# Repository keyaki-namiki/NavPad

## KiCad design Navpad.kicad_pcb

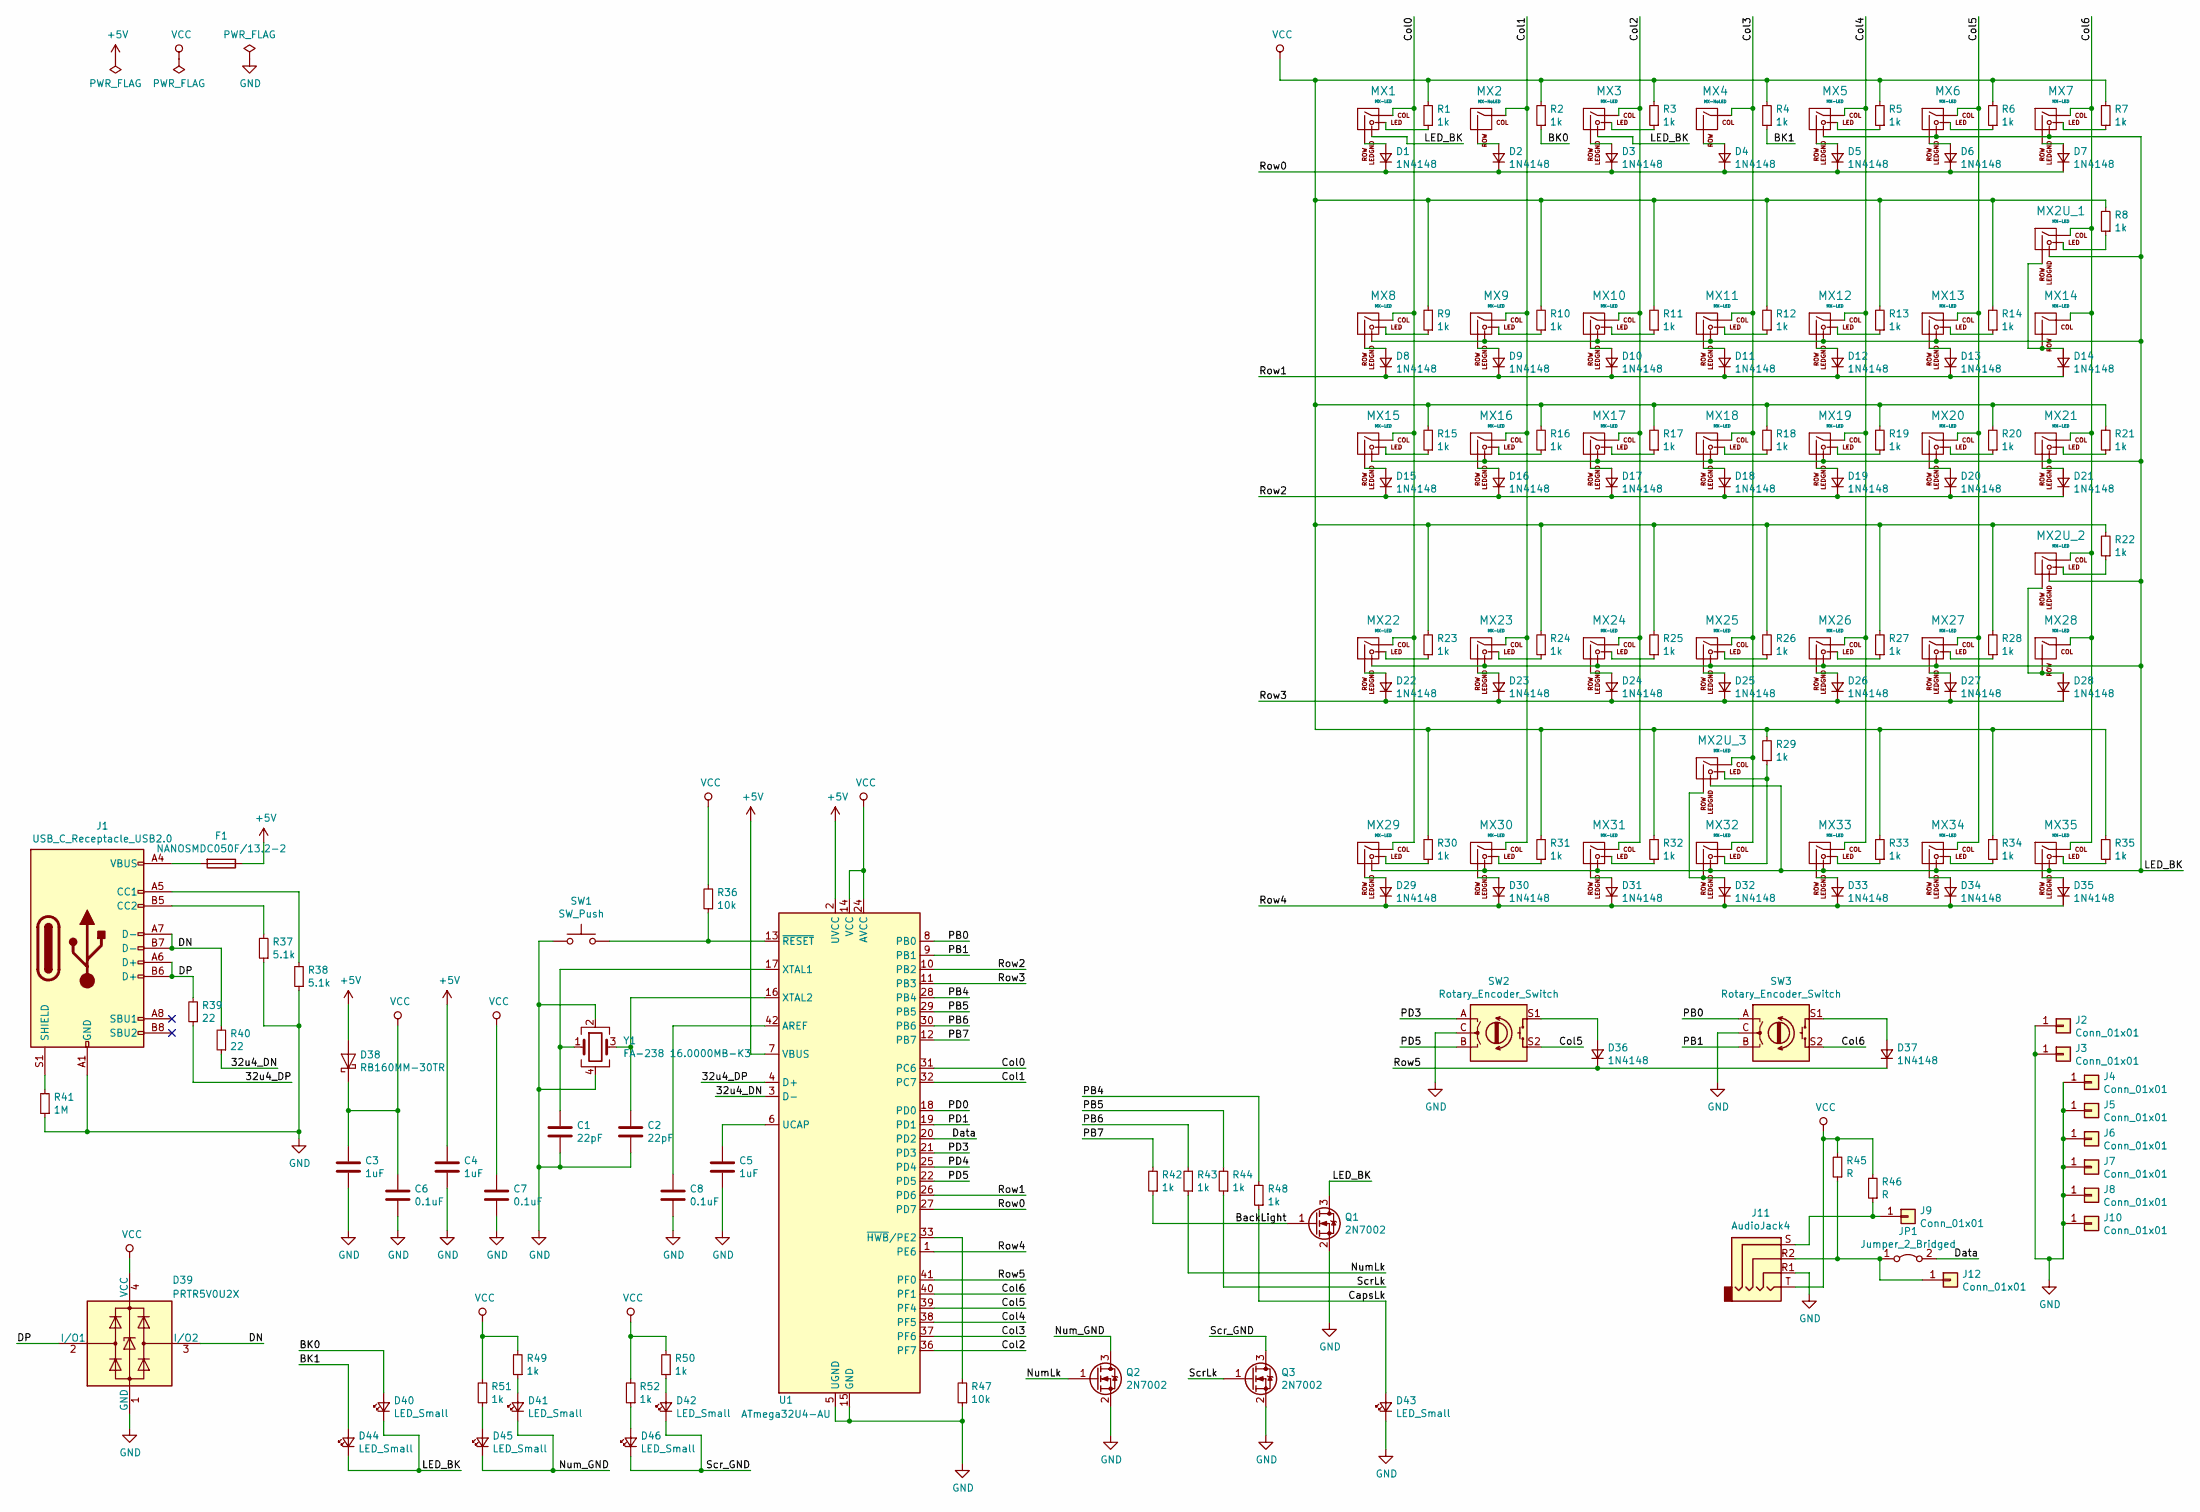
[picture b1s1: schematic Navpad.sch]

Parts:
C1, C2: 22pF; C_0603_1608Metric_Pad1.05x0.95mm_HandSolder
C3, C4, C5: 1uF; C_0603_1608Metric_Pad1.05x0.95mm_HandSolder
C6, C7, C8: 0.1uF; C_0603_1608Metric_Pad1.05x0.95mm_HandSolder
D1, D2, D3, D4, D5, D6, D7, D8, D9, D10, D11, D12, D13, D14, D15, D16, D17, D18, D19, D20, D21, D22, D23, D24, D25, D26, D27, D28, D29, D30, D31, D32, D33, D34, D35, D36, D37: 1N4148; D_SOD-123F
D38: RB160MM-30TR; D_SOD-123F
D39: PRTR5V0U2X; SOT-143
D40, D41, D42, D43, D44, D45, D46: LED_Small; LED_0603_1608Metric_Pad1.05x0.95mm_HandSolder
F1: NANOSMDC050F/13.2-2; Fuse_1206_3216Metric_Pad1.42x1.75mm_HandSolder
J1: USB_C_Receptacle_USB2.0; USB_C_Receptacle_GCT_USB4085
J2, J3: Conn_01x01; TestPoint_Plated_Hole_D5.0mm
J4, J5, J6, J7, J8, J10: Conn_01x01; MountingHole_2.2mm_M2_Pad
J9, J12: Conn_01x01; TestPoint_THTPad_1.0x1.0mm_Drill0.5mm
J11: AudioJack4; 4pin_jack
JP1: Jumper_2_Bridged; SolderJumper-2_P1.3mm_Bridged_Pad1.0x1.5mm
MX1, MX3, MX5, MX6, MX7, MX8, MX9, MX10, MX11, MX12, MX13, MX15, MX16, MX17, MX18, MX19, MX20, MX21, MX22, MX23, MX24, MX25, MX26, MX27, MX29, MX30, MX31, MX32, MX33, MX34, MX35: MX-LED; MXOnly-1U
MX2, MX4: MX-NoLED; MXOnly-1U-NoLED
MX2U_1, MX2U_2, MX2U_3: MX-LED; MXOnly-2U-ReversedStabilizers
MX14, MX28: MX-LED; MXOnly-1U-NoLED
Q1, Q2, Q3: 2N7002; SOT-23
R1, R2, R3, R4, R5, R6, R7, R8, R9, R10, R11, R12, R13, R14, R15, R16, R17, R18, R19, R20, R21, R22, R23, R24, R25, R26, R27, R28, R29, R30, R31, R32, R33, R34, R35, R42, R43, R44, R48, R49, R50, R51, R52: 1k; R_0603_1608Metric_Pad1.05x0.95mm_HandSolder
R36, R47: 10k; R_0603_1608Metric_Pad1.05x0.95mm_HandSolder
R37, R38: 5.1k; R_0603_1608Metric_Pad1.05x0.95mm_HandSolder
R39, R40: 22; R_0603_1608Metric_Pad1.05x0.95mm_HandSolder
R41: 1M; R_0603_1608Metric_Pad1.05x0.95mm_HandSolder
R45, R46: R; R_0603_1608Metric_Pad1.05x0.95mm_HandSolder
SW1: SW_Push; SW_SPST_TL3342
SW2, SW3: Rotary_Encoder_Switch; RotaryEncoder_Alps_EC11E-Switch_Vertical_H20mm
U1: ATmega32U4-AU; TQFP-44_10x10mm_P0.8mm
Y1: FA-238 16.0000MB-K3; Crystal_SMD_SeikoEpson_FA238-4Pin_3.2x2.5mm_HandSoldering

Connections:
+5V: C4.1, D38.2 (A), F1.1, U1.2 (UVCC), U1.7 (VBUS)
/32u4_DN: R40.1, U1.3 (D-)
/32u4_DP: R39.1, U1.4 (D+)
/BK0: D40.2 (A), R2.1
/BK1: D44.2 (A), R4.1
/BackLight: Q1.1 (G), R42.1
/CapsLk: D43.2 (A), R48.1
/Col0: MX1.1 (COL), MX8.1 (COL), MX15.1 (COL), MX22.1 (COL), MX29.1 (COL), U1.31 (PC6)
/Col1: MX2.1 (COL), MX9.1 (COL), MX16.1 (COL), MX23.1 (COL), MX30.1 (COL), U1.32 (PC7)
/Col2: MX3.1 (COL), MX10.1 (COL), MX17.1 (COL), MX24.1 (COL), MX31.1 (COL), U1.36 (PF7)
/Col3: MX2U_3.1 (COL), MX4.1 (COL), MX11.1 (COL), MX18.1 (COL), MX25.1 (COL), MX32.1 (COL), U1.37 (PF6)
/Col4: MX5.1 (COL), MX12.1 (COL), MX19.1 (COL), MX26.1 (COL), MX33.1 (COL), U1.38 (PF5)
/Col5: MX6.1 (COL), MX13.1 (COL), MX20.1 (COL), MX27.1 (COL), MX34.1 (COL), SW2.S2, U1.39 (PF4)
/Col6: MX2U_1.1 (COL), MX2U_2.1 (COL), MX7.1 (COL), MX14.1 (COL), MX21.1 (COL), MX28.1 (COL), MX35.1 (COL), SW3.S2, U1.40 (PF1)
/DN: D39.3 (I/O2), J1.A7 (D-), J1.B7 (D-), R40.2
/DP: D39.2 (I/O1), J1.A6 (D+), J1.B6 (D+), R39.2
/Data: JP1.2 (B), U1.20 (PD2)
/LED_BK: D40.1 (K), D44.1 (K), MX1.4 (LEDGND), MX2U_1.4 (LEDGND), MX2U_2.4 (LEDGND), MX2U_3.4 (LEDGND), MX3.4 (LEDGND), MX5.4 (LEDGND), MX6.4 (LEDGND), MX7.4 (LEDGND), MX8.4 (LEDGND), MX9.4 (LEDGND), MX10.4 (LEDGND), MX11.4 (LEDGND), MX12.4 (LEDGND), MX13.4 (LEDGND), MX15.4 (LEDGND), MX16.4 (LEDGND), MX17.4 (LEDGND), MX18.4 (LEDGND), MX19.4 (LEDGND), MX20.4 (LEDGND), MX21.4 (LEDGND), MX22.4 (LEDGND), MX23.4 (LEDGND), MX24.4 (LEDGND), MX25.4 (LEDGND), MX26.4 (LEDGND), MX27.4 (LEDGND), MX29.4 (LEDGND), MX30.4 (LEDGND), MX31.4 (LEDGND), MX32.4 (LEDGND), MX33.4 (LEDGND), MX34.4 (LEDGND), MX35.4 (LEDGND), Q1.3 (D)
/NumLk: Q2.1 (G), R43.1
/Num_GND: D41.1 (K), D45.1 (K), Q2.3 (D)
/PB0: SW3.A, U1.8 (PB0)
/PB1: SW3.B, U1.9 (PB1)
/PB4: R48.2, U1.28 (PB4)
/PB5: R44.2, U1.29 (PB5)
/PB6: R43.2, U1.30 (PB6)
/PB7: R42.2, U1.12 (PB7)
/PD0: U1.18 (PD0)
/PD1: U1.19 (PD1)
/PD3: SW2.A, U1.21 (PD3)
/PD4: U1.25 (PD4)
/PD5: SW2.B, U1.22 (PD5)
/Row0: D1.1 (K), D2.1 (K), D3.1 (K), D4.1 (K), D5.1 (K), D6.1 (K), D7.1 (K), U1.27 (PD7)
/Row1: D8.1 (K), D9.1 (K), D10.1 (K), D11.1 (K), D12.1 (K), D13.1 (K), D14.1 (K), U1.26 (PD6)
/Row2: D15.1 (K), D16.1 (K), D17.1 (K), D18.1 (K), D19.1 (K), D20.1 (K), D21.1 (K), U1.10 (PB2)
/Row3: D22.1 (K), D23.1 (K), D24.1 (K), D25.1 (K), D26.1 (K), D27.1 (K), D28.1 (K), U1.11 (PB3)
/Row4: D29.1 (K), D30.1 (K), D31.1 (K), D32.1 (K), D33.1 (K), D34.1 (K), D35.1 (K), U1.1 (PE6)
/Row5: D36.1 (K), D37.1 (K), U1.41 (PF0)
/ScrLk: Q3.1 (G), R44.1
/Scr_GND: D42.1 (K), D46.1 (K), Q3.3 (D)
GND: C1.2, C2.2, C3.2, C4.2, C5.2, C6.2, C7.2, C8.2, D39.1 (GND), D43.1 (K), J1.A1 (GND), J1.A12 (GND), J1.B1 (GND), J1.B12 (GND), J2.1, J3.1, J4.1, J5.1, J6.1, J7.1, J8.1, J10.1, J11.R1, Q1.2 (S), Q2.2 (S), Q3.2 (S), R37.1, R38.1, R41.1, R47.1, SW1.1, SW2.C, SW3.C, U1.5 (UGND), U1.15 (GND), U1.23 (GND), U1.35 (GND), U1.43 (GND), Y1.2, Y1.4
unnamed: C1.1, U1.17 (XTAL1), Y1.1
unnamed: C2.1, U1.16 (XTAL2), Y1.3
unnamed: C5.1, U1.6 (UCAP)
unnamed: C8.1, U1.42 (AREF)
unnamed: D1.2 (A), MX1.2 (ROW)
unnamed: D2.2 (A), MX2.2 (ROW)
unnamed: D3.2 (A), MX3.2 (ROW)
unnamed: D4.2 (A), MX4.2 (ROW)
unnamed: D5.2 (A), MX5.2 (ROW)
unnamed: D6.2 (A), MX6.2 (ROW)
unnamed: D7.2 (A), MX7.2 (ROW)
unnamed: D8.2 (A), MX8.2 (ROW)
unnamed: D9.2 (A), MX9.2 (ROW)
unnamed: D10.2 (A), MX10.2 (ROW)
unnamed: D11.2 (A), MX11.2 (ROW)
unnamed: D12.2 (A), MX12.2 (ROW)
unnamed: D13.2 (A), MX13.2 (ROW)
unnamed: D14.2 (A), MX2U_1.2 (ROW), MX14.2 (ROW)
unnamed: D15.2 (A), MX15.2 (ROW)
unnamed: D16.2 (A), MX16.2 (ROW)
unnamed: D17.2 (A), MX17.2 (ROW)
unnamed: D18.2 (A), MX18.2 (ROW)
unnamed: D19.2 (A), MX19.2 (ROW)
unnamed: D20.2 (A), MX20.2 (ROW)
unnamed: D21.2 (A), MX21.2 (ROW)
unnamed: D22.2 (A), MX22.2 (ROW)
unnamed: D23.2 (A), MX23.2 (ROW)
unnamed: D24.2 (A), MX24.2 (ROW)
unnamed: D25.2 (A), MX25.2 (ROW)
unnamed: D26.2 (A), MX26.2 (ROW)
unnamed: D27.2 (A), MX27.2 (ROW)
unnamed: D28.2 (A), MX2U_2.2 (ROW), MX28.2 (ROW)
unnamed: D29.2 (A), MX29.2 (ROW)
unnamed: D30.2 (A), MX30.2 (ROW)
unnamed: D31.2 (A), MX31.2 (ROW)
unnamed: D32.2 (A), MX2U_3.2 (ROW), MX32.2 (ROW)
unnamed: D33.2 (A), MX33.2 (ROW)
unnamed: D34.2 (A), MX34.2 (ROW)
unnamed: D35.2 (A), MX35.2 (ROW)
unnamed: D36.2 (A), SW2.S1
unnamed: D37.2 (A), SW3.S1
unnamed: D41.2 (A), R49.1
unnamed: D42.2 (A), R50.1
unnamed: D45.2 (A), R51.1
unnamed: D46.2 (A), R52.1
unnamed: F1.2, J1.A4 (VBUS), J1.A9 (VBUS), J1.B4 (VBUS), J1.B9 (VBUS)
unnamed: J1.A5 (CC1), R38.2
unnamed: J1.B5 (CC2), R37.2
unnamed: J1.S1 (SHIELD), R41.2
unnamed: J11.R2, J12.1, JP1.1 (A), R45.1
unnamed: J9.1, J11.S, R46.1
unnamed: MX1.3 (LED), R1.1
unnamed: MX2U_1.3 (LED), R8.1
unnamed: MX2U_2.3 (LED), R22.1
unnamed: MX2U_3.3 (LED), MX32.3 (LED), R29.1
unnamed: MX3.3 (LED), R3.1
unnamed: MX5.3 (LED), R5.1
unnamed: MX6.3 (LED), R6.1
unnamed: MX7.3 (LED), R7.1
unnamed: MX8.3 (LED), R9.1
unnamed: MX9.3 (LED), R10.1
unnamed: MX10.3 (LED), R11.1
unnamed: MX11.3 (LED), R12.1
unnamed: MX12.3 (LED), R13.1
unnamed: MX13.3 (LED), R14.1
unnamed: MX15.3 (LED), R15.1
unnamed: MX16.3 (LED), R16.1
unnamed: MX17.3 (LED), R17.1
unnamed: MX18.3 (LED), R18.1
unnamed: MX19.3 (LED), R19.1
unnamed: MX20.3 (LED), R20.1
unnamed: MX21.3 (LED), R21.1
unnamed: MX22.3 (LED), R23.1
unnamed: MX23.3 (LED), R24.1
unnamed: MX24.3 (LED), R25.1
unnamed: MX25.3 (LED), R26.1
unnamed: MX26.3 (LED), R27.1
unnamed: MX27.3 (LED), R28.1
unnamed: MX29.3 (LED), R30.1
unnamed: MX30.3 (LED), R31.1
unnamed: MX31.3 (LED), R32.1
unnamed: MX33.3 (LED), R33.1
unnamed: MX34.3 (LED), R34.1
unnamed: MX35.3 (LED), R35.1
unnamed: R36.1, SW1.2, U1.13 (~RESET)
unnamed: R47.2, U1.33 (~HWB~/PE2)
VCC: C3.1, C6.1, C7.1, D38.1 (K), D39.4 (VCC), J11.T, R1.2, R2.2, R3.2, R4.2, R5.2, R6.2, R7.2, R8.2, R9.2, R10.2, R11.2, R12.2, R13.2, R14.2, R15.2, R16.2, R17.2, R18.2, R19.2, R20.2, R21.2, R22.2, R23.2, R24.2, R25.2, R26.2, R27.2, R28.2, R29.2, R30.2, R31.2, R32.2, R33.2, R34.2, R35.2, R36.2, R45.2, R46.2, R49.2, R50.2, R51.2, R52.2, U1.14 (VCC), U1.24 (AVCC), U1.34 (VCC), U1.44 (AVCC)

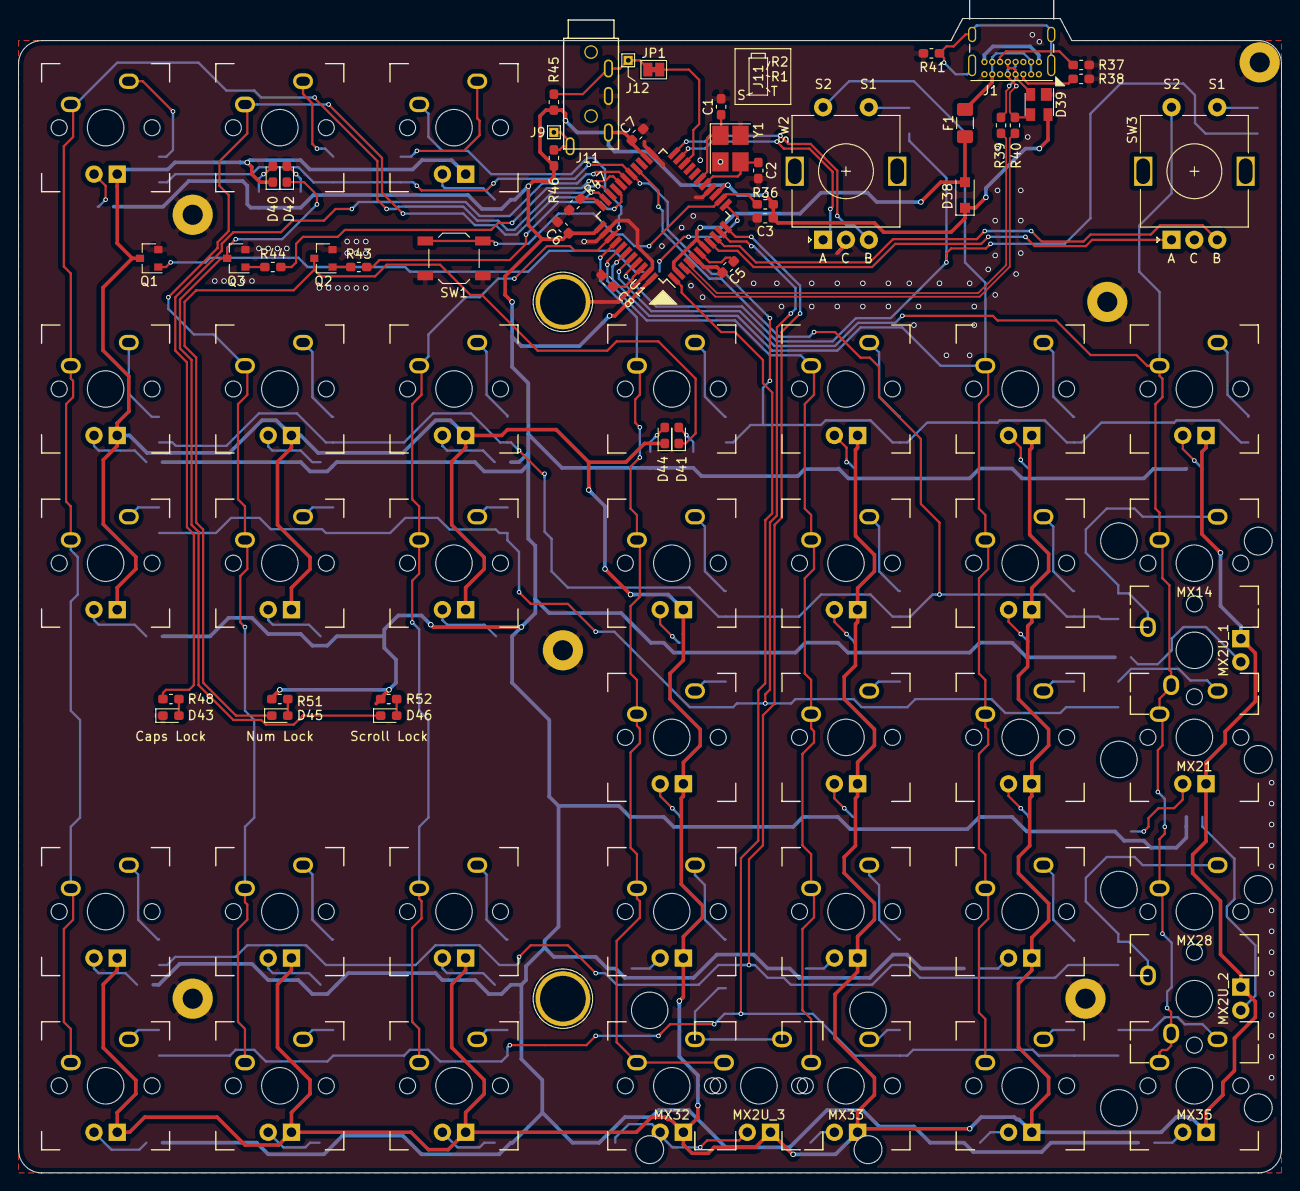
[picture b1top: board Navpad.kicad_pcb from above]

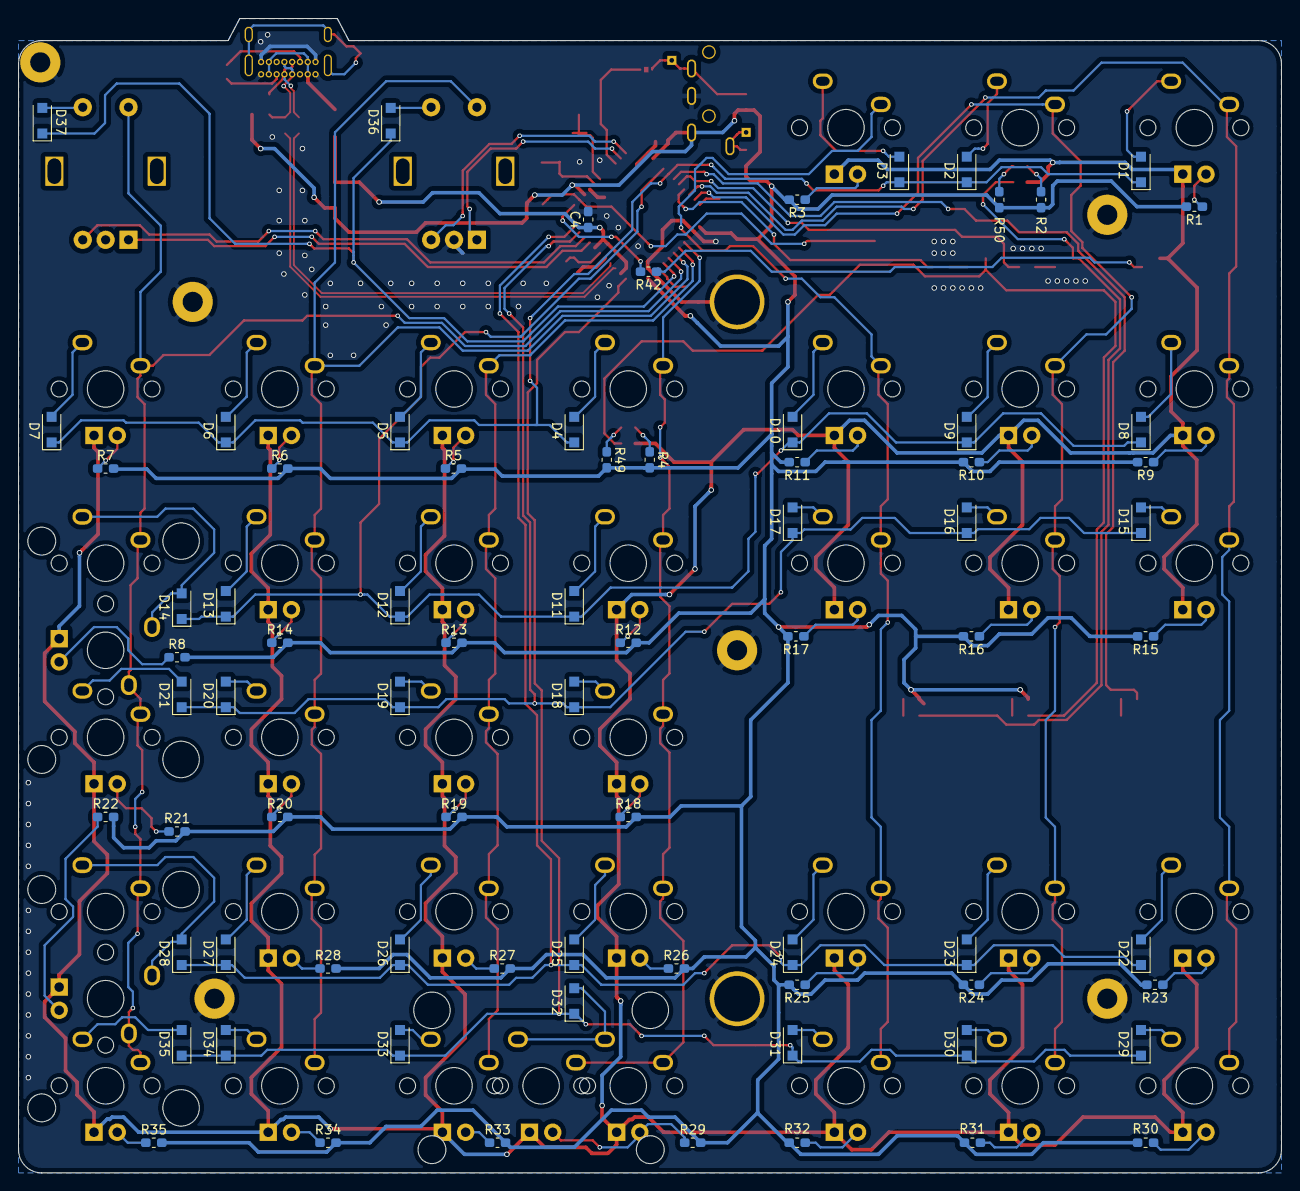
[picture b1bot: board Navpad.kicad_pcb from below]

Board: 2 copper layers, 138.1 x 126.2 mm, 166 parts (76 on the bottom side), 124 nets.
